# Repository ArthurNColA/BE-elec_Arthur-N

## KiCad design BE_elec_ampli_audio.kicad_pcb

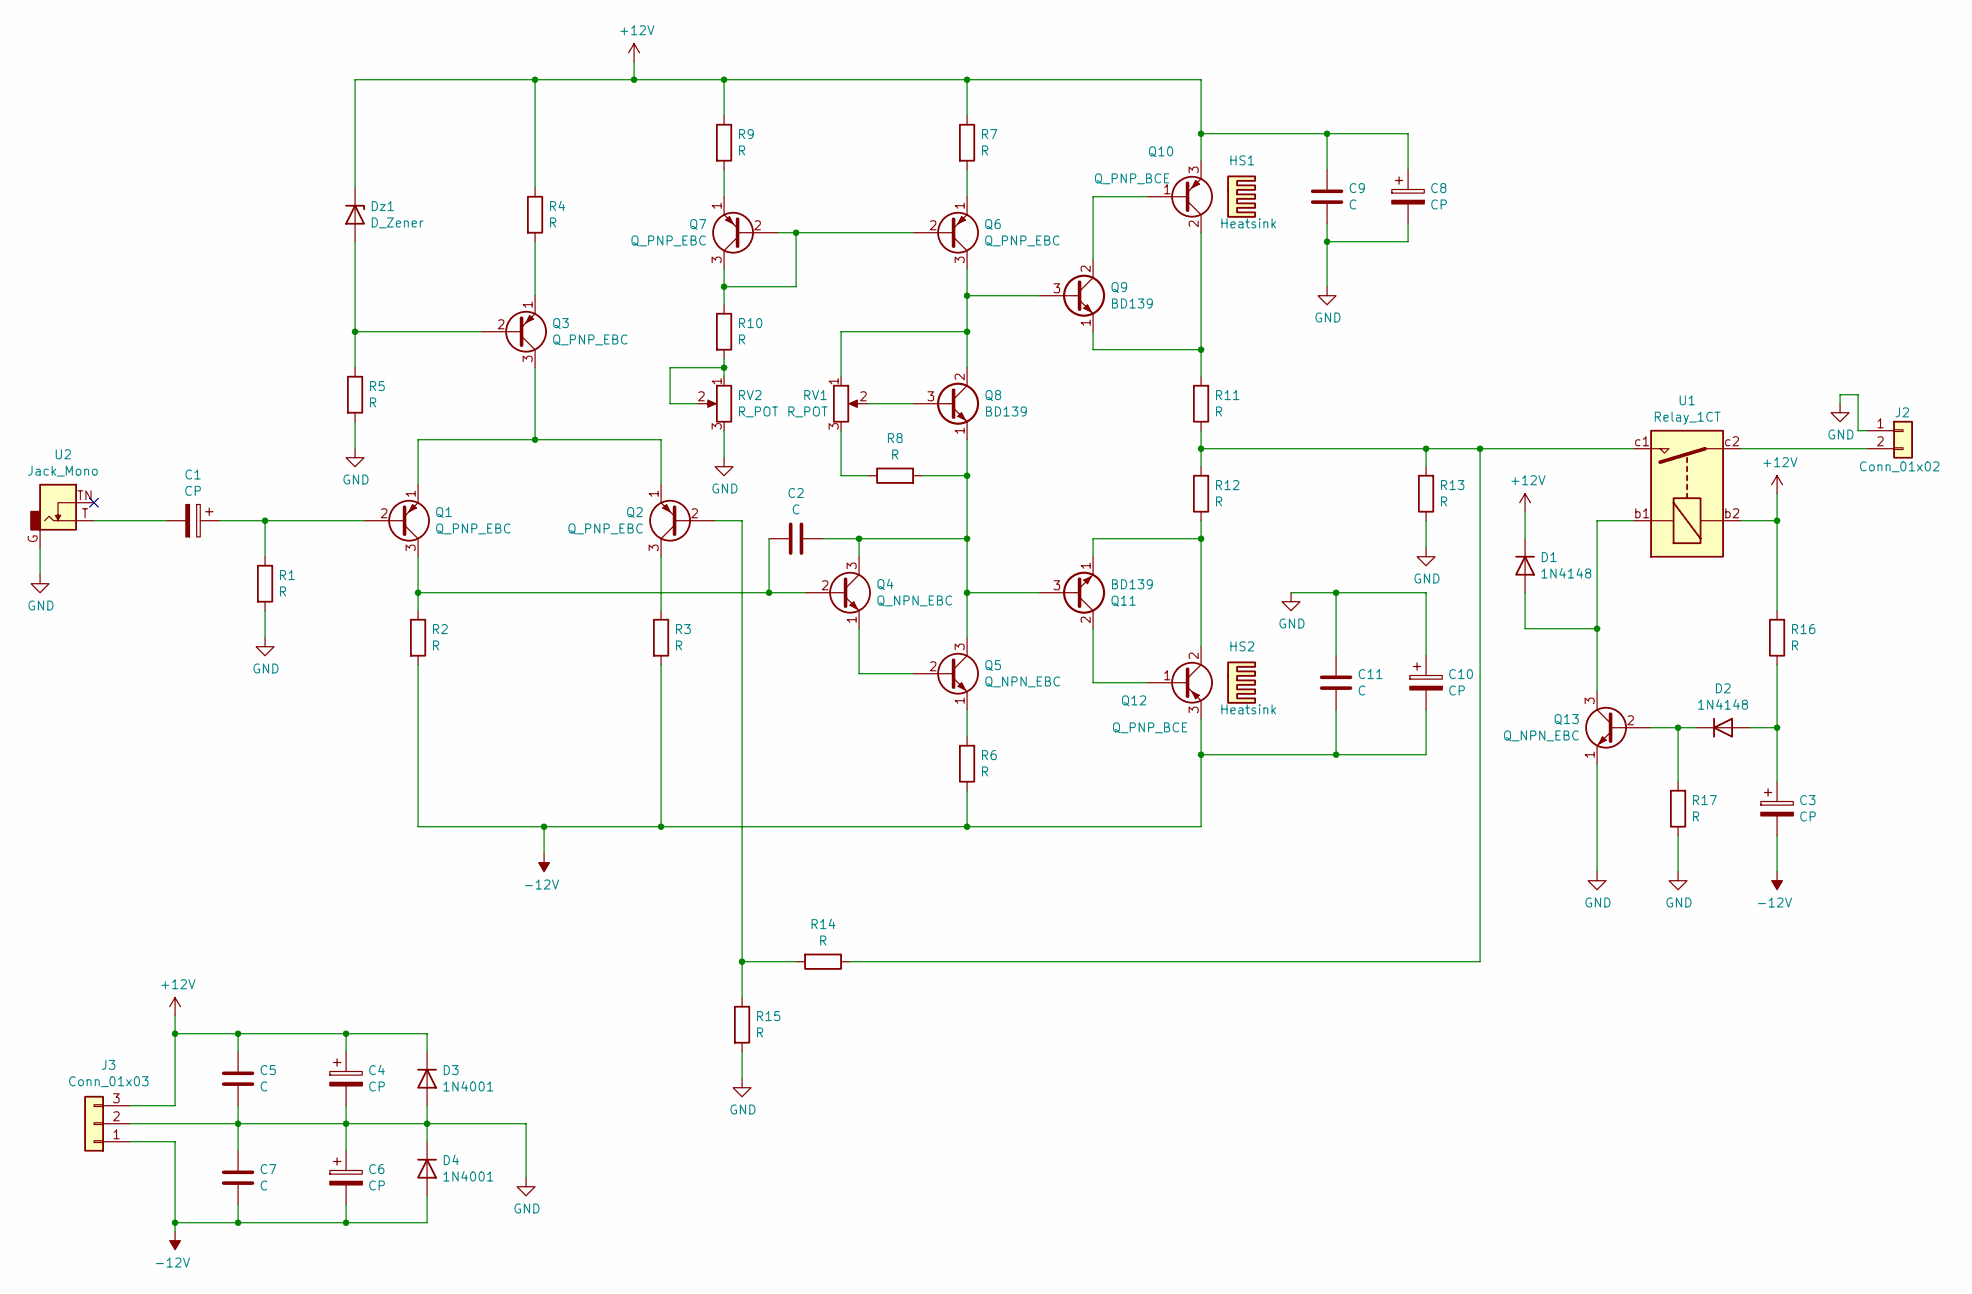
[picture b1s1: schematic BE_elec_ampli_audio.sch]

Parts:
C1, C3, C4, C6: CP; CP_Radial_D8.0mm_P5.00mm
C2, C5, C7, C9, C11: C; C_Rect_L7.2mm_W3.5mm_P5.00mm_FKS2_FKP2_MKS2_MKP2
C8, C10: CP; CP_Radial_D12.5mm_P5.00mm
D1, D2: 1N4148; D_DO-35_SOD27_P10.16mm_Horizontal
D3, D4: 1N4001; D_DO-35_SOD27_P10.16mm_Horizontal
Dz1: D_Zener; D_DO-35_SOD27_P10.16mm_Horizontal
HS1, HS2: Heatsink; Heatsink_Fischer_SK104-STC-STIC_35x13mm_2xDrill2.5mm
J2: Conn_01x02; PhoenixContact_MSTBVA_2,5_2-G-5,08_1x02_P5.08mm_Vertical
J3: Conn_01x03; PhoenixContact_MSTBVA_2,5_3-G-5,08_1x03_P5.08mm_Vertical
Q1, Q2, Q3, Q6, Q7: Q_PNP_EBC; TO-18-3
Q4, Q5, Q13: Q_NPN_EBC; TO-18-3
Q8, Q9, Q11: BD139; TO-126-3_Vertical
Q10, Q12: Q_PNP_BCE; TO-220-3_Vertical
R1, R2, R3, R4, R5, R6, R7, R8, R9, R10, R13, R14, R15, R16, R17: R; R_Axial_DIN0207_L6.3mm_D2.5mm_P10.16mm_Horizontal
R11, R12: R; R_Axial_DIN0516_L15.5mm_D5.0mm_P20.32mm_Horizontal
RV1, RV2: R_POT; Potentiometer_Bourns_3296W_Vertical
U1: Relay_1CT; Relay_be
U2: Jack_Mono; Jack_35RAPC2AV

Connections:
+12V: C4.1, C5.2, C8.1, C9.2, D1.1 (K), D3.1 (K), Dz1.1 (K), J3.3, Q10.3 (E), R4.1, R7.1, R9.1, R16.2, U1.b2
-12V: C3.2, C6.2, C7.1, C10.2, C11.1, D4.2 (A), J3.1, Q12.3 (E), R2.2, R3.2, R6.1
GND: C4.2, C5.1, C6.1, C7.2, C8.2, C9.1, C10.1, C11.2, D3.2 (A), D4.1 (K), J2.1, J3.2, Q13.1 (E), R1.2, R5.2, R13.1, R15.2, R17.1, RV2.3, U2.G
unnamed: C1.1, Q1.2 (B), R1.1
unnamed: C1.2, U2.T
unnamed: C2.1, Q4.3 (C), Q5.3 (C), Q8.1 (E), Q11.3 (B), R8.2
unnamed: C2.2, Q1.3 (C), Q4.2 (B), R2.1
unnamed: C3.1, D2.2 (A), R16.1
unnamed: D1.2 (A), Q13.3 (C), U1.b1
unnamed: D2.1 (K), Q13.2 (B), R17.2
unnamed: Dz1.2 (A), Q3.2 (B), R5.1
unnamed: J2.2, U1.c2
unnamed: Q1.1 (E), Q2.1 (E), Q3.3 (C)
unnamed: Q2.2 (B), R14.2, R15.1
unnamed: Q2.3 (C), R3.1
unnamed: Q3.1 (E), R4.2
unnamed: Q4.1 (E), Q5.2 (B)
unnamed: Q5.1 (E), R6.2
unnamed: Q6.1 (E), R7.2
unnamed: Q6.2 (B), Q7.2 (B), Q7.3 (C), R10.1
unnamed: Q6.3 (C), Q8.2 (C), Q9.3 (B), RV1.1
unnamed: Q7.1 (E), R9.2
unnamed: Q8.3 (B), RV1.2
unnamed: Q9.2 (C), Q10.1 (B)
unnamed: Q9.1 (E), Q10.2 (C), R11.2
unnamed: Q11.1 (E), Q12.2 (C), R12.1
unnamed: Q11.2 (C), Q12.1 (B)
unnamed: R8.1, RV1.3
unnamed: R10.2, RV2.1, RV2.2
unnamed: R11.1, R12.2, R13.2, R14.1, U1.c1

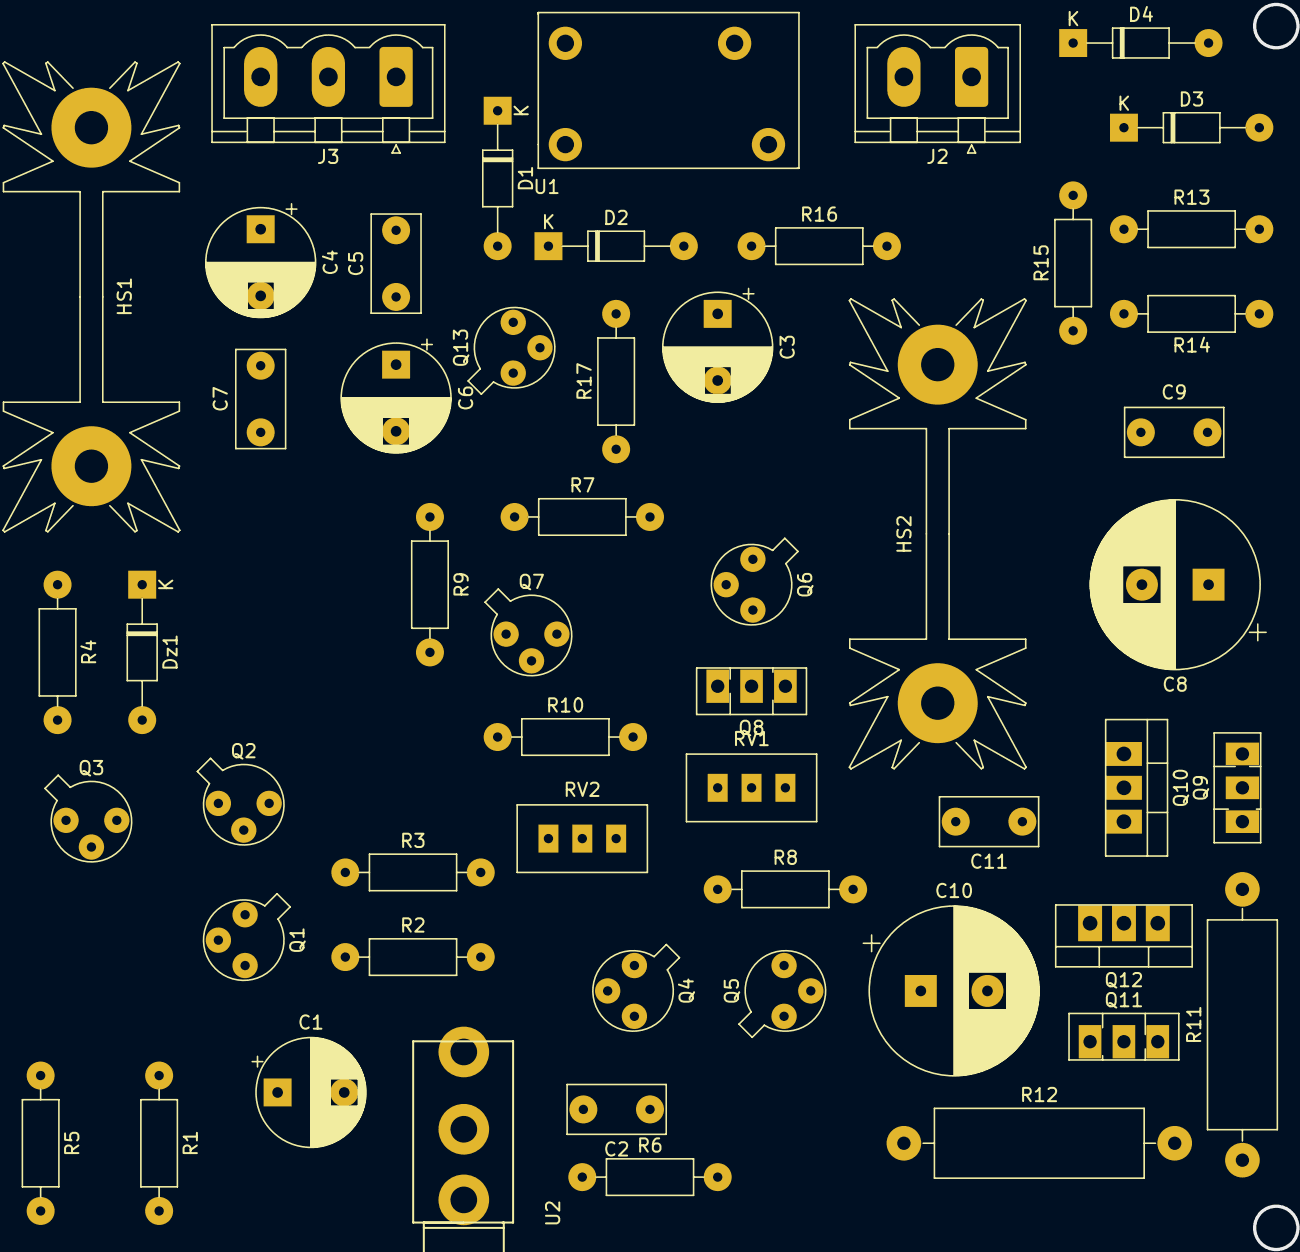
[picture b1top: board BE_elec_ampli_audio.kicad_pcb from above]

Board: 2 copper layers, 54 parts (0 on the bottom side), 30 nets.

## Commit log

2021-04-06 librairie pour trouber relais
2021-04-06 NETLIST
2021-04-06 Kicad_pcb
2021-04-06 .net
2021-04-06 .pro
2021-04-06 .sch
2021-04-06 info-cache
2021-04-06 lib-table
2021-04-06 li_be
2021-04-06 kicad_pcb-bak
2021-04-06 sch-bak
2021-04-06 sym-lib-table
2021-04-11 .sch-bak
2021-04-11 pcb-bak
